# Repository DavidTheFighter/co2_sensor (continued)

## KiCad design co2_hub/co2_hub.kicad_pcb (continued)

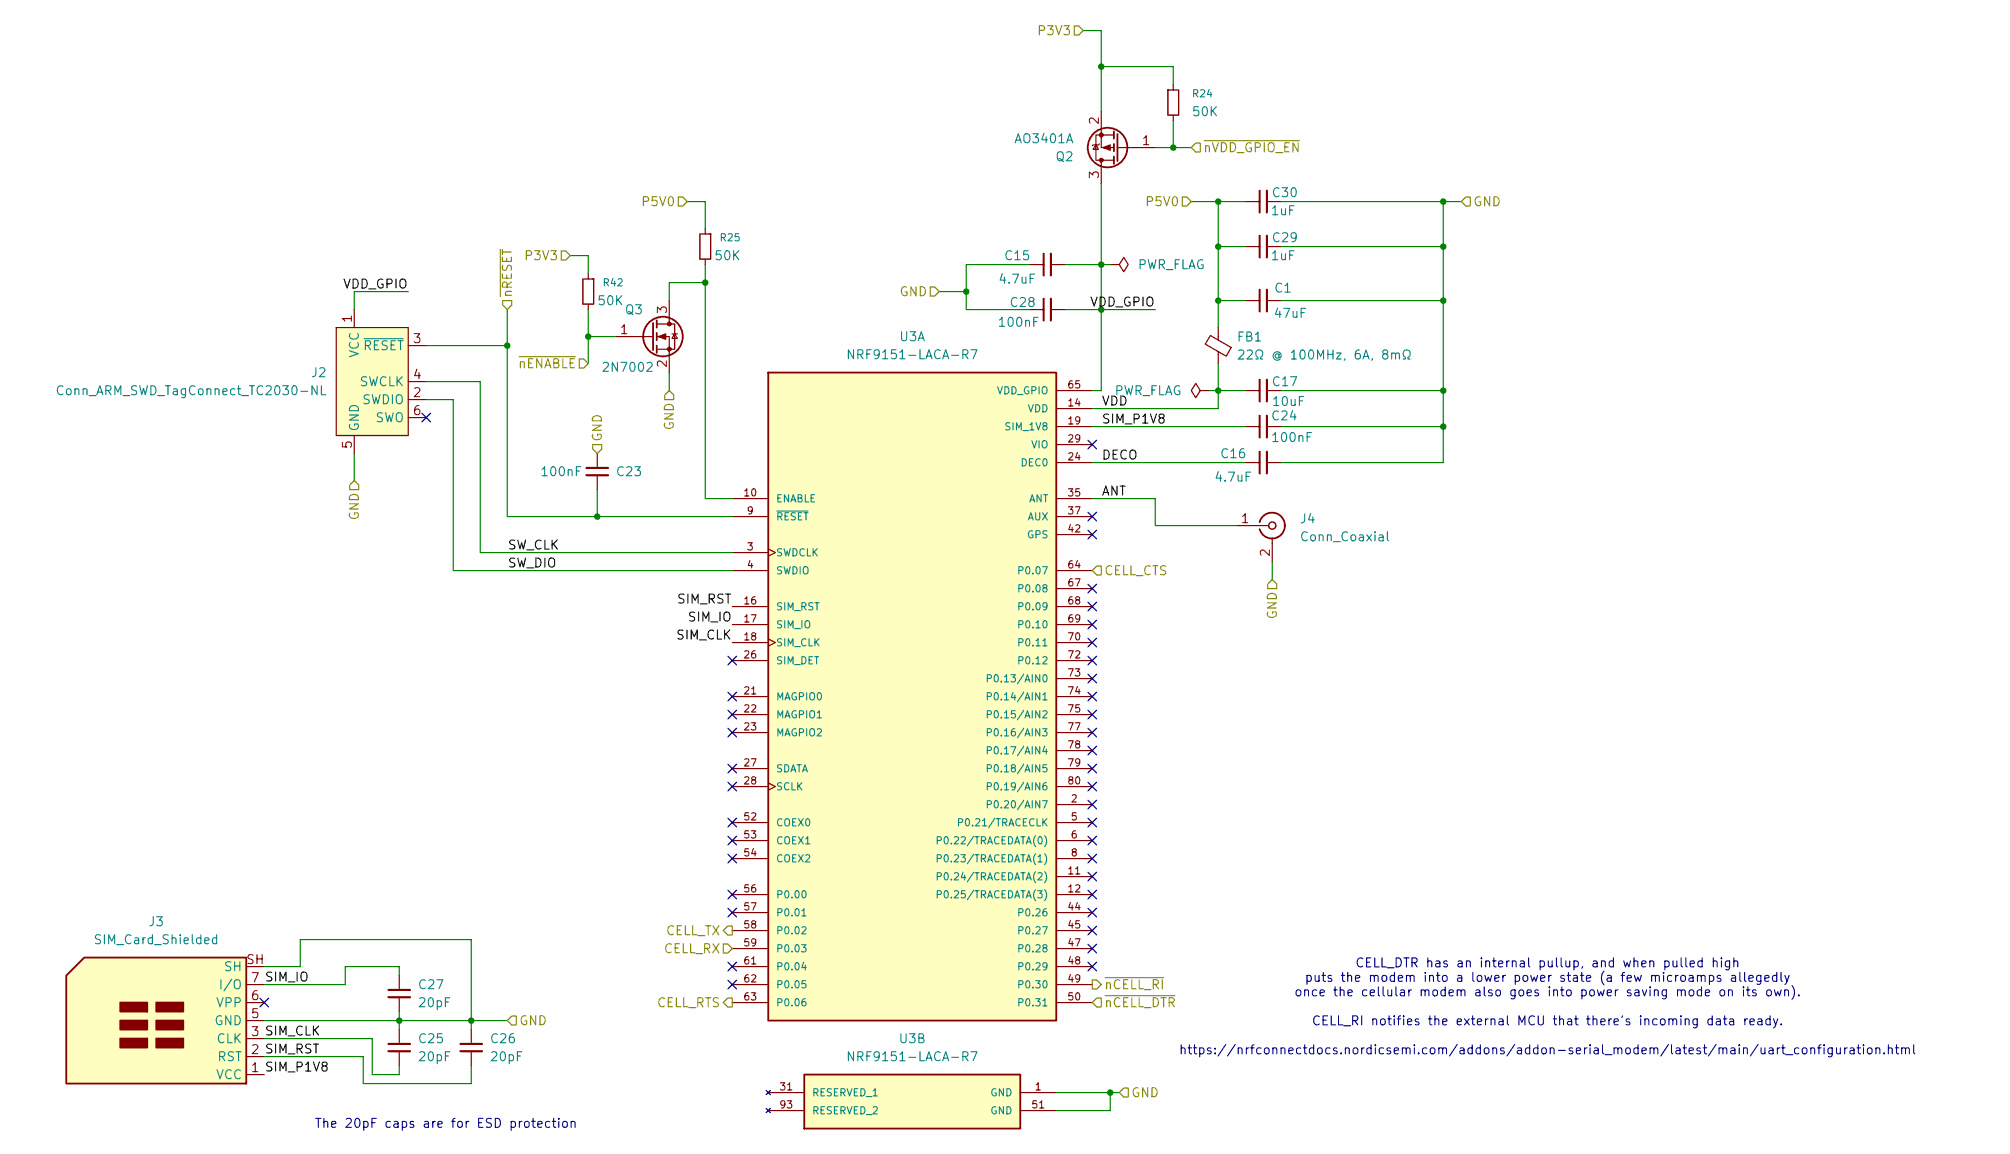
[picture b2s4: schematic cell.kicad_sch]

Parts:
C1: 47uF; C_1206_3216Metric; LCSC C96123
C15, C16: 4.7uF; C_0603_1608Metric; LCSC C19666
C17: 10uF; C_0805_2012Metric; LCSC C15850
C23, C24, C28: 100nF; C_0402_1005Metric; LCSC C1525
C25, C26, C27: 20pF; C_0402_1005Metric; LCSC C1554
C29, C30: 1uF; C_0603_1608Metric; LCSC C15849
FB1: 22Ω @ 100MHz, 6A, 8mΩ; L_0805_2012Metric; LCSC C361652
J2: Conn_ARM_SWD_TagConnect_TC2030-NL; Tag-Connect_TC2030-IDC-NL_2x03_P1.27mm_Vertical
J3: SIM_Card_Shielded; XUNPU Nano-SIM Push-Push With Card Detect; LCSC C7529384
J4: Conn_Coaxial; SMA_Samtec_SMA-J-P-H-ST-EM1_EdgeMount
Q2: AO3401A; SOT-23; LCSC C15127
Q3: 2N7002; SOT-23; LCSC C8545
R24, R25, R42: 50K; R_0402_1005Metric; LCSC C25794
U3: NRF9151-LACA-R7; Nordic_nRF9151-LAxx_LGA-80-33EP_12.1x11.1mm_P0.5mm; PARTREV 2025-10-21

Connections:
/MCU/LPUART1_CTS: U3.63 (P0.06); also elsewhere on the board
/MCU/LPUART1_RTS: U3.64 (P0.07); also elsewhere on the board
/MCU/LPUART1_RX: U3.58 (P0.02); also elsewhere on the board
/MCU/LPUART1_TX: U3.59 (P0.03); also elsewhere on the board
/MCU/~nCELL_DTR: U3.50 (P0.31); also elsewhere on the board
/MCU/~nCELL_ENABLE: Q3.1 (G), R42.2; also elsewhere on the board
/MCU/~nCELL_RI: U3.49 (P0.30); also elsewhere on the board
/MCU/~nCELL_VDD_GPIO_ENABLE: Q2.1 (G), R24.2; also elsewhere on the board
/P3V3: Q2.2 (S), R24.1, R42.1; also elsewhere on the board
/P5V0: C1.1, C29.1, C30.1, FB1.2, R25.1; also elsewhere on the board
/cell/ANT: J4.1 (In), U3.35 (ANT)
/cell/DECO: C16.1, U3.24 (DEC0)
/cell/SIM_CLK: C25.2, J3.3 (CLK), U3.18 (SIM_CLK)
/cell/SIM_IO: C27.1, J3.7 (I/O), U3.17 (SIM_IO)
/cell/SIM_P1V8: C24.2, J3.1 (VCC), U3.19 (SIM_1V8)
/cell/SIM_RST: C26.2, J3.2 (RST), U3.16 (SIM_RST)
/cell/SW_CLK: J2.4 (SWCLK), U3.3 (SWDCLK)
/cell/SW_DIO: J2.2 (SWDIO), U3.4 (SWDIO)
/cell/VDD: C17.1, FB1.1, U3.14 (VDD)
/cell/VDD_GPIO: C15.2, C28.2, J2.1 (VCC), Q2.3 (D), U3.65 (VDD_GPIO)
/cell/~nRESET: C23.2, J2.3 (~RESET), U3.9 (~RESET); also elsewhere on the board
GND: C1.2, C15.1, C16.2, C17.2, C23.1, C24.1, C25.1, C26.1, C27.2, C28.1, C29.2, C30.2, J2.5 (GND), J3.5 (GND), J3.SH, J4.2 (Ext), Q3.2 (S), U3.1 (GND), U3.7 (GND), U3.13 (GND), U3.15 (GND), U3.20 (GND), U3.25 (GND), U3.30 (GND), U3.34 (GND), U3.36 (GND), U3.38 (GND), U3.39 (GND), U3.40 (GND), U3.41 (GND), U3.43 (GND), U3.46 (GND), U3.51 (GND), U3.55 (GND), U3.60 (GND), U3.66 (GND), U3.71 (GND), U3.76 (GND), U3.105 (GND), U3.106 (GND), U3.107 (GND), U3.108 (GND), U3.109 (GND), U3.110 (GND), U3.111 (GND), U3.112 (GND), U3.113 (GND); also elsewhere on the board
unnamed: Q3.3 (D), R25.2, U3.10 (ENABLE)

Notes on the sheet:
CELL_DTR has an internal pullup, and when pulled high puts the modem into a lower power state (a few microamps allegedly once the cellular modem also goes into power saving mode on its own). CELL_RI notifies the external MCU that there's incoming data ready. https://nrfconnectdocs.nordicsemi.com/ad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
The 20pF caps are for ESD protection

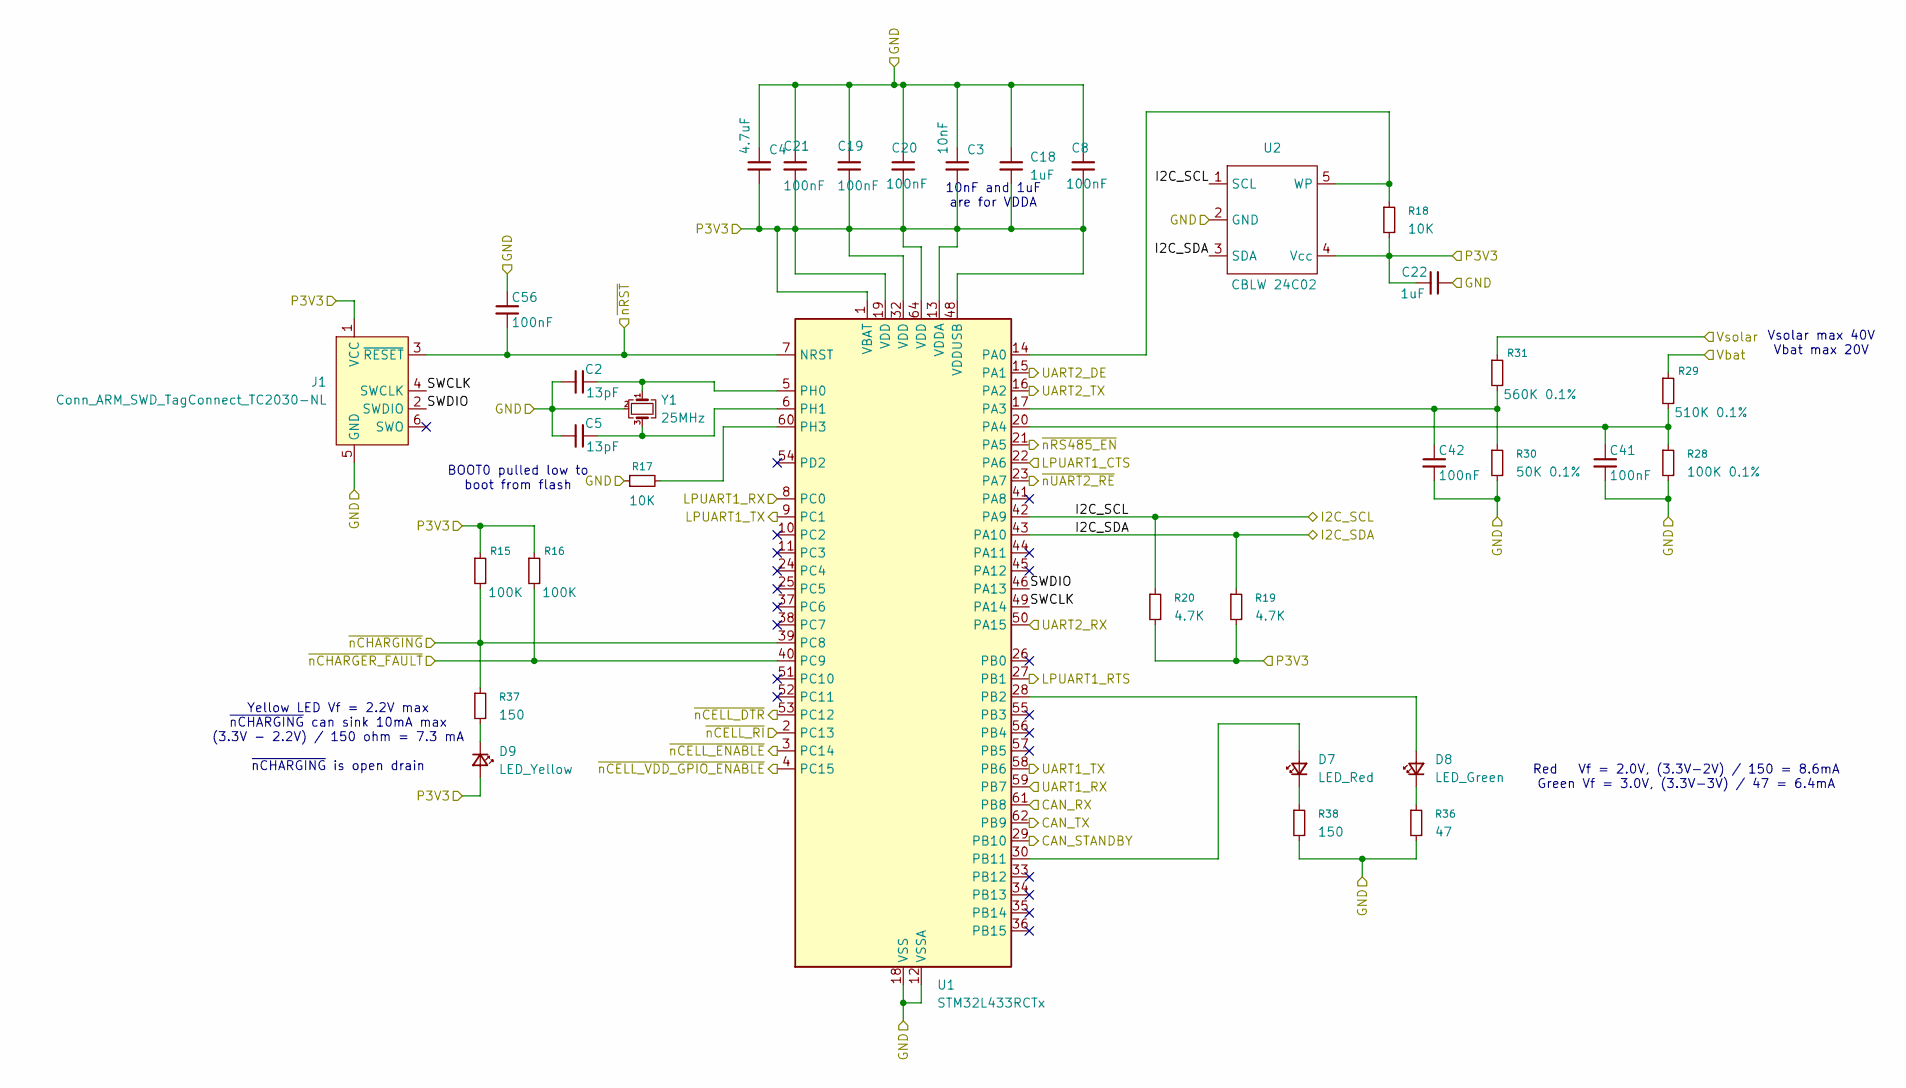
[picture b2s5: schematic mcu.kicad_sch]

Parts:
C2, C5: 13pF; C_0402_1005Metric; LCSC C1547
C3: 10nF; C_0402_1005Metric; LCSC C15195
C4: 4.7uF; C_0603_1608Metric; LCSC C19666
C8, C19, C20, C21, C41, C42, C56: 100nF; C_0402_1005Metric; LCSC C1525
C18, C22: 1uF; C_0603_1608Metric; LCSC C15849
D7: LED_Red; LED_0805_2012Metric; LCSC C84256
D8: LED_Green; LED_0805_2012Metric; LCSC C2297
D9: LED_Yellow; LED_0805_2012Metric; LCSC C2296
J1: Conn_ARM_SWD_TagConnect_TC2030-NL; Tag-Connect_TC2030-IDC-NL_2x03_P1.27mm_Vertical
R15, R16: 100K; R_0603_1608Metric; LCSC C25803
R17, R18: 10K; R_0402_1005Metric; LCSC C25744
R19, R20: 4.7K; R_0402_1005Metric; LCSC C25900
R28: 100K 0.1%; R_0603_1608Metric; LCSC C122538
R29: 510K 0.1%; R_0603_1608Metric; LCSC C861452
R30: 50K 0.1%; R_0603_1608Metric; LCSC C861451
R31: 560K 0.1%; R_0603_1608Metric; LCSC C719312
R36: 47; R_0603_1608Metric; LCSC C23182
R37, R38: 150; R_0603_1608Metric; LCSC C22808
U1: STM32L433RCTx; LQFP-64_10x10mm_P0.5mm; LCSC C160656
U2: CBLW 24C02; SOT-23-5; LCSC C18723540
Y1: 25MHz; Crystal_SMD_3225-4Pin_3.2x2.5mm; LCSC C251614

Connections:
/CAN/RX: U1.61 (PB8); also elsewhere on the board
/CAN/STANDBY: U1.29 (PB10); also elsewhere on the board
/CAN/TX: U1.62 (PB9); also elsewhere on the board
/DBG_UART_RX: U1.59 (PB7); also elsewhere on the board
/DBG_UART_TX: U1.58 (PB6); also elsewhere on the board
/I2C_SCL: R20.1, U1.42 (PA9), U2.1 (SCL); also elsewhere on the board
/I2C_SDA: R19.1, U1.43 (PA10), U2.3 (SDA); also elsewhere on the board
/MCU/LPUART1_CTS: U1.22 (PA6); also elsewhere on the board
/MCU/LPUART1_RTS: U1.27 (PB1); also elsewhere on the board
/MCU/LPUART1_RX: U1.8 (PC0); also elsewhere on the board
/MCU/LPUART1_TX: U1.9 (PC1); also elsewhere on the board
/MCU/SWCLK: J1.4 (SWCLK), U1.49 (PA14)
/MCU/SWDIO: J1.2 (SWDIO), U1.46 (PA13)
/MCU/UART2_DE: U1.15 (PA1); also elsewhere on the board
/MCU/UART2_RX: U1.50 (PA15); also elsewhere on the board
/MCU/UART2_TX: U1.16 (PA2); also elsewhere on the board
/MCU/~nCELL_DTR: U1.53 (PC12); also elsewhere on the board
/MCU/~nCELL_ENABLE: U1.3 (PC14); also elsewhere on the board
/MCU/~nCELL_RI: U1.2 (PC13); also elsewhere on the board
/MCU/~nCELL_VDD_GPIO_ENABLE: U1.4 (PC15); also elsewhere on the board
/MCU/~nCHARGER_FAULT: R16.2, U1.40 (PC9); also elsewhere on the board
/MCU/~nCHARGING: R15.2, R37.1, U1.39 (PC8); also elsewhere on the board
/MCU/~nRS485_EN: U1.21 (PA5); also elsewhere on the board
/MCU/~nRST: C56.2, J1.3 (~RESET), U1.7 (NRST); also elsewhere on the board
/MCU/~nUART2_RE: U1.23 (PA7); also elsewhere on the board
/P3V3: C3.2, C4.2, C8.2, C18.2, C19.2, C20.2, C21.2, C22.1, D9.2 (A), J1.1 (VCC), R15.1, R16.1, R18.2, R19.2, R20.2, U1.1 (VBAT), U1.13 (VDDA), U1.19 (VDD), U1.32 (VDD), U1.48 (VDDUSB), U1.64 (VDD), U2.4 (Vcc); also elsewhere on the board
/Vbus: R29.1; also elsewhere on the board
/Vsolar: R31.1; also elsewhere on the board
GND: C2.1, C3.1, C4.1, C5.1, C8.1, C18.1, C19.1, C20.1, C21.1, C22.2, C41.2, C42.2, C56.1, J1.5 (GND), R17.1, R28.2, R30.2, R36.2, R38.2, U1.12 (VSSA), U1.18 (VSS), U1.31 (VSS), U1.47 (VSS), U1.63 (VSS), U2.2 (GND), Y1.2 (G), Y1.4 (G); also elsewhere on the board
unnamed: D7.2 (A), U1.30 (PB11)
unnamed: D7.1 (K), R38.1
unnamed: D8.2 (A), U1.28 (PB2)
unnamed: D8.1 (K), R36.1
unnamed: D9.1 (K), R37.2
unnamed: R18.1, U1.14 (PA0), U2.5 (WP)
unnamed: C42.1, R30.1, R31.2, U1.17 (PA3)
unnamed: C41.1, R28.1, R29.2, U1.20 (PA4)
unnamed: C2.2, U1.5 (PH0), Y1.1
unnamed: C5.2, U1.6 (PH1), Y1.3
unnamed: R17.2, U1.60 (PH3)

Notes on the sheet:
Red Vf = 2.0V, (3.3V-2V) / 150 = 8.6mA Green Vf = 3.0V, (3.3V-3V) / 47 = 6.4mA
Yellow LED Vf = 2.2V max ~{nCHARGING} can sink 10mA max (3.3V - 2.2V) / 150 ohm = 7.3 mA ~{nCHARGING} is open drain
10nF and 1uF are for VDDA
BOOT0 pulled low to boot from flash
Vsolar max 40V Vbat max 20V

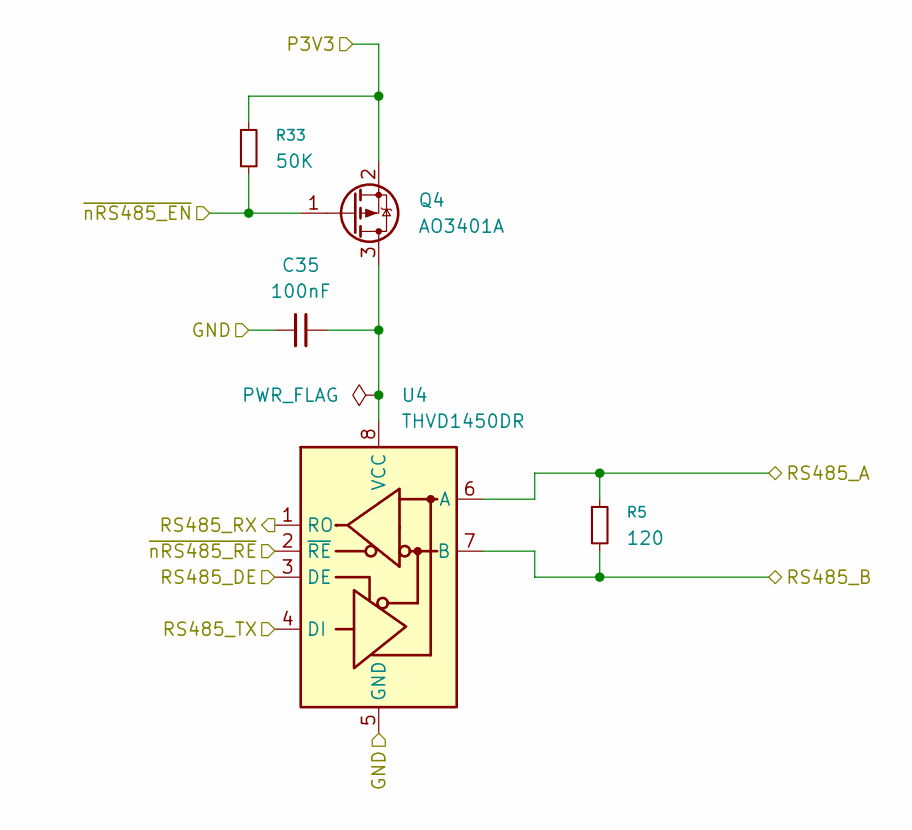
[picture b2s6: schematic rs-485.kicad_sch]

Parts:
C35: 100nF; C_0402_1005Metric; LCSC C1525
Q4: AO3401A; SOT-23; LCSC C15127
R5: 120; R_0603_1608Metric; LCSC C22787
R33: 50K; R_0402_1005Metric; LCSC C25794
U4: THVD1450DR; VSON-8-1EP_3x3mm_P0.65mm_EP1.6x2.4mm

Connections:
/MCU/UART2_DE: U4.3 (DE); also elsewhere on the board
/MCU/UART2_RX: U4.1 (RO); also elsewhere on the board
/MCU/UART2_TX: U4.4 (DI); also elsewhere on the board
/MCU/~nRS485_EN: Q4.1 (G), R33.2; also elsewhere on the board
/MCU/~nUART2_RE: U4.2 (~RE); also elsewhere on the board
/P3V3: Q4.2 (S), R33.1; also elsewhere on the board
/RS485_A: R5.1, U4.6 (A); also elsewhere on the board
/RS485_B: R5.2, U4.7 (B); also elsewhere on the board
GND: C35.1, U4.5 (GND); also elsewhere on the board
unnamed: C35.2, Q4.3 (D), U4.8 (VCC)

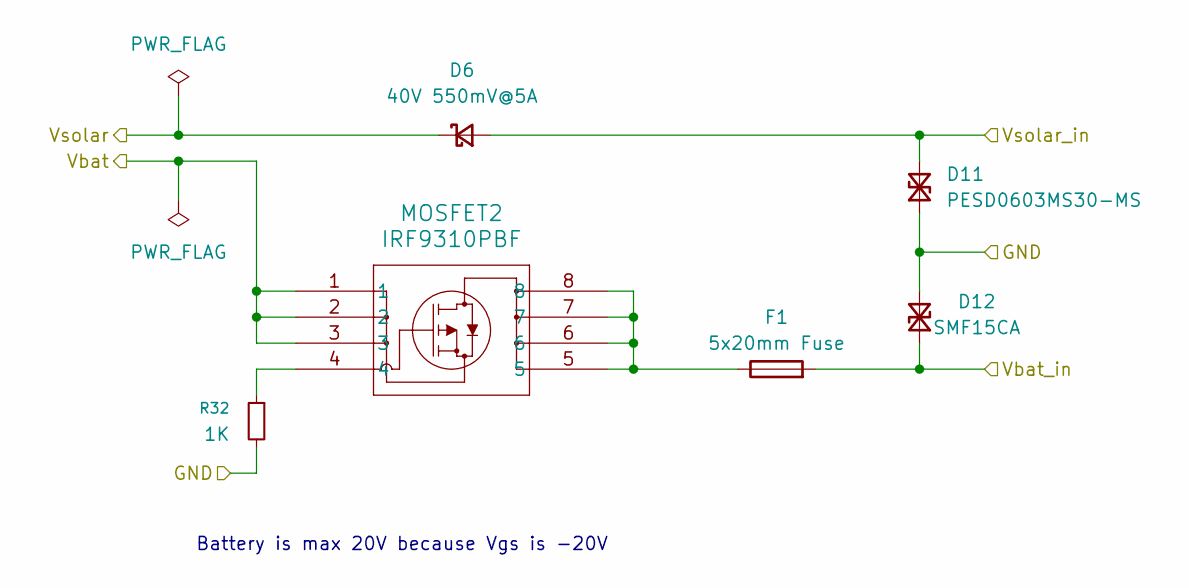
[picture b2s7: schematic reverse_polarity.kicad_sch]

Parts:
D6: 40V 550mV@5A; D_SMA; LCSC C22452
D11: PESD0603MS30-MS; D_0603_1608Metric; LCSC C7473181
D12: SMF15CA; D_SOD-123F; LCSC C19077510
F1: 5x20mm Fuse; Fuseholder_Clip-5x20mm_Bel_FC-203-22_Lateral_P17.80x5.00mm_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
MOSFET2: IRF9310PBF; SO-8_3.9x4.9mm_P1.27mm; LCSC C5236693
R32: 1K; R_0603_1608Metric; LCSC C21190

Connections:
/Vbat: MOSFET2.1, MOSFET2.2, MOSFET2.3; also elsewhere on the board
/Vbat_in: D12.1 (A1), F1.2; also elsewhere on the board
/Vsolar: D6.1 (K); also elsewhere on the board
/Vsolar_in: D6.2 (A), D11.2 (A2); also elsewhere on the board
GND: D11.1 (A1), D12.2 (A2), R32.2; also elsewhere on the board
unnamed: F1.1, MOSFET2.5, MOSFET2.6, MOSFET2.7, MOSFET2.8
unnamed: MOSFET2.4, R32.1

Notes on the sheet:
Battery is max 20V because Vgs is -20V

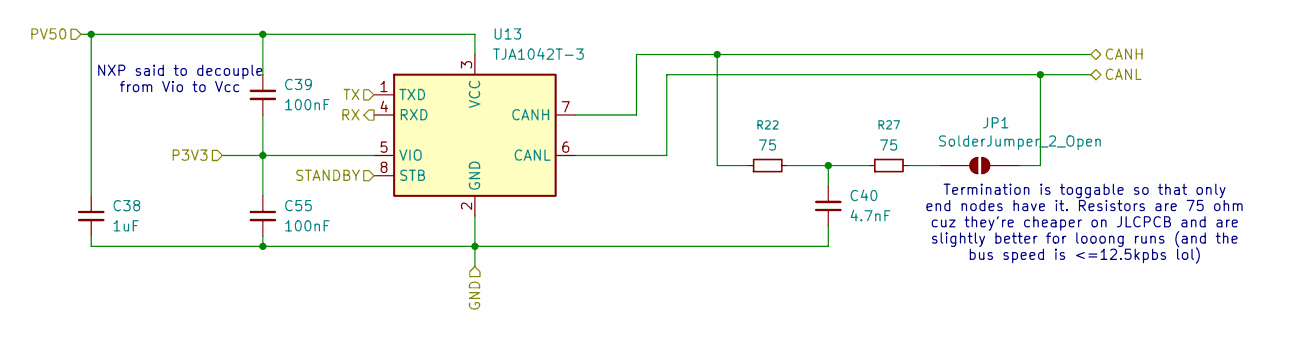
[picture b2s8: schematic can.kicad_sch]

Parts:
C38: 1uF; C_0603_1608Metric; LCSC C15849
C39, C55: 100nF; C_0402_1005Metric; LCSC C1525
C40: 4.7nF; C_0805_2012Metric; LCSC C1744
JP1: SolderJumper_2_Open; SolderJumper-2_P1.3mm_Open_TrianglePad1.0x1.5mm
R22, R27: 75; R_0603_1608Metric; LCSC C4275
U13: TJA1042T-3; SOIC-8_3.9x4.9mm_P1.27mm; LCSC C132227

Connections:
/CAN/RX: U13.4 (RXD); also elsewhere on the board
/CAN/STANDBY: U13.8 (STB); also elsewhere on the board
/CAN/TX: U13.1 (TXD); also elsewhere on the board
/CANH: R22.1, U13.7 (CANH); also elsewhere on the board
/CANL: JP1.2 (B), U13.6 (CANL); also elsewhere on the board
/P3V3: C39.2, C55.1, U13.5 (VIO); also elsewhere on the board
/P5V0: C38.1, C39.1, U13.3 (VCC); also elsewhere on the board
GND: C38.2, C40.2, C55.2, U13.2 (GND); also elsewhere on the board
unnamed: C40.1, R22.2, R27.1
unnamed: JP1.1 (A), R27.2

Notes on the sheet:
Termination is toggable so that only end nodes have it. Resistors are 75 ohm cuz they're cheaper on JLCPCB and are slightly better for looong runs (and the bus speed is <=12.5kpbs lol)
NXP said to decouple from Vio to Vcc

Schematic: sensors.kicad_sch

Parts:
C12, C13: 100nF; C_0402_1005Metric; LCSC C1525
U5: MS5611-01BA; LGA-8_3x5mm_P1.25mm; LCSC C15639
U6: SHT4x; Sensirion_DFN-4_1.5x1.5mm_P0.8mm_SHT4x_NoCentralPad; LCSC C2909890

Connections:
/I2C_SCL: U5.8 (SCLK), U6.2 (SCL); also elsewhere on the board
/I2C_SDA: U5.7 (SDI/SDA), U6.1 (SDA); also elsewhere on the board
/P3V3: C12.1, C13.1, U5.1 (VDD), U5.2 (PS), U6.3 (VDD); also elsewhere on the board
GND: C12.2, C13.2, U5.3 (GND), U5.4 (CSB), U5.5 (CSB), U6.4 (VSS); also elsewhere on the board

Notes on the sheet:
I2C = 1000100
CSB in I2C defines the I2C address LOW = 1110111
PS tied high for I2C mode

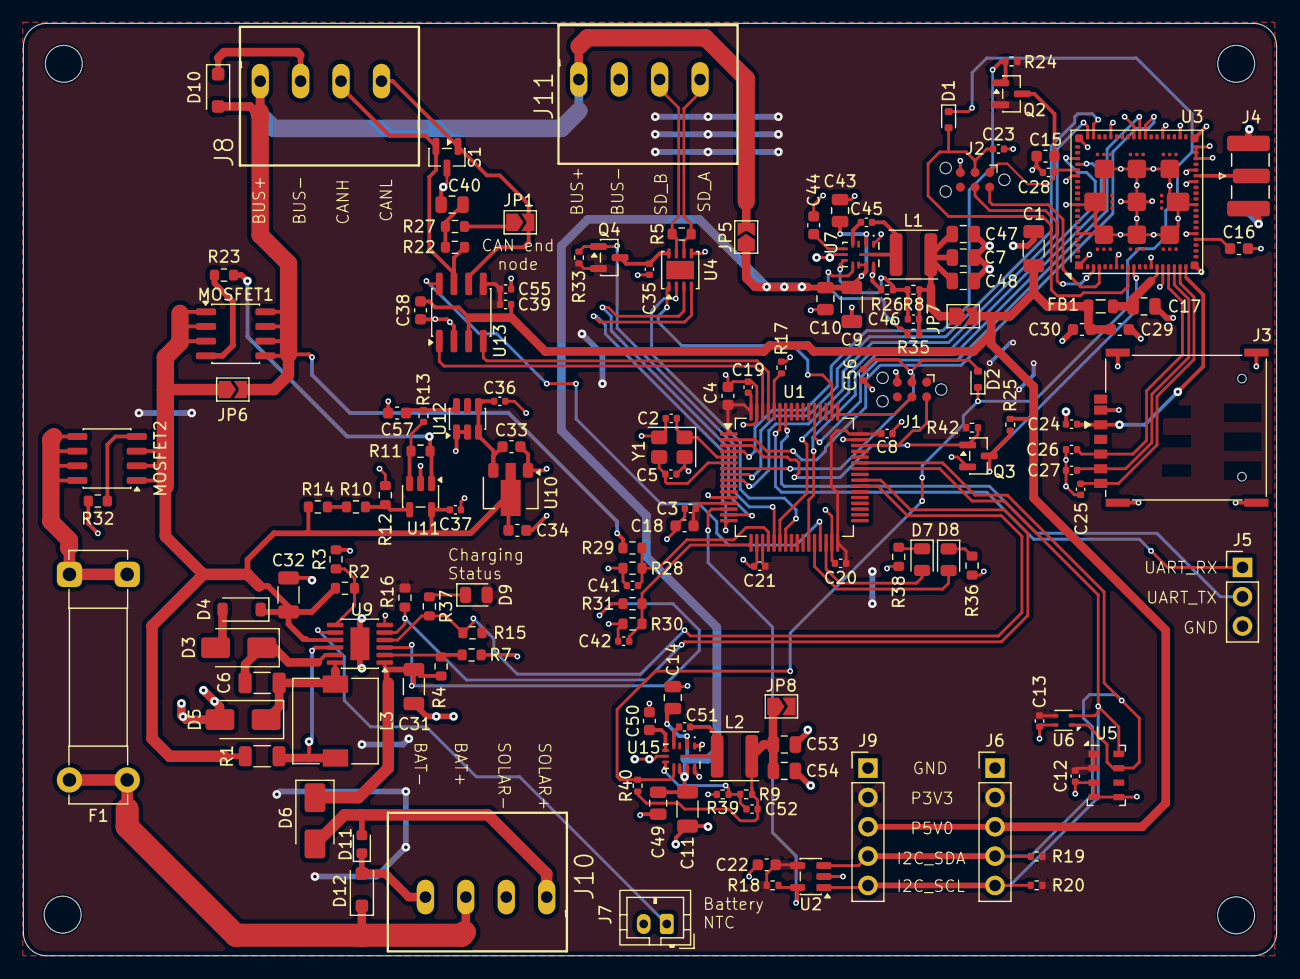
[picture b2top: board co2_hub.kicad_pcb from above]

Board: 4 copper layers, 108.5 x 80.7 mm, 152 parts (0 on the bottom side), 92 nets.

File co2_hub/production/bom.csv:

Designator,Footprint,Quantity,Value,LCSC Part #
C1,1206,1,47uF,C96123
"C10, C14, C43, C49",0805,4,220nF,C5378
"C11, C9",1206,2,4.7uF,C29823
"C12, C13, C19, C20, C21, C23, C24, C28, C35, C36, C37, C39, C41, C42, C45, C51, C55, C56, C8",0402,19,100nF,C1525
"C15, C16, C4",0603,3,4.7uF,C19666
"C17, C47, C48, C53, C54",0805,5,10uF,C15850
"C18, C22, C29, C30, C33, C34, C38, C44, C50, C57",0603,10,1uF,C15849
"C2, C5",0402,2,13pF,C1547
"C25, C26, C27, C46, C52",0402,5,20pF,C1554
C3,0402,1,10nF,C15195
"C31, C32",1206,2,10uF,C13585
C40,0805,1,4.7nF,C1744
C6,1206,1,1uF,C1848
C7,0805,1,22uF,C45783
"D1, D2",D_SOD-523,2,40V 0.3V@0.2A,C135802
"D10, D12",D_SOD-123F,2,SMF15CA,C19077510
D11,0603,1,PESD0603MS30-MS,C7473181
D3,D_SMA,1,40V 550mV@3A,C8678
D4,D_SOD-123,1,Zener 6.2V,C22435091
"D5, D6",D_SMA,2,40V 550mV@5A,C22452
D7,0805,1,LED_Red,C84256
D8,0805,1,LED_Green,C2297
D9,0805,1,LED_Yellow,C2296
F1,Fuseholder_Clip-5x20mm_Bel_FC-203-22_Lateral_P17.80x5.00mm_D1.17mm_Horizontal,1,5x20mm Fuse,
FB1,0805,1,"22Ω @ 100MHz, 6A, 8mΩ",C361652
"J10, J11, J8",WAGO-250-104,3,Conn_01x04,
J3,XUNPU Nano-SIM Push-Push With Card Detect,1,SIM_Card_Shielded,C7529384
J4,SMA_Samtec_SMA-J-P-H-ST-EM1_EdgeMount,1,Conn_Coaxial,
J5,PinHeader_1x03_P2.54mm_Vertical,1,Conn_01x03,
"J6, J9",PinHeader_1x05_P2.54mm_Vertical,2,Conn_01x05,
J7,JST_PH_B2B-PH-K_1x02_P2.00mm_Vertical,1,Conn_01x02,
"L1, L2",L_Changjiang_FNR4030S,2,10uH,C167879
L3,L_7.3x7.3_H4.5,1,10uH,C19268627
"MOSFET1, MOSFET2",SO-8_3.9x4.9mm_P1.27mm,2,IRF9310PBF,C5236693
"Q2, Q4",SOT-23,2,AO3401A,C15127
Q3,SOT-23,1,2N7002,C8545
R1,1206,1,0.05,C7467249
R10,0603,1,887K 0.1%,C2984370
R11,0603,1,4.64M 1%,C482862
"R12, R28",0603,2,100K 0.1%,C122538
"R13, R17, R18",0402,3,10K,C25744
R14,0603,1,16.2K 0.1%,C728602
"R15, R16, R7",0603,3,100K,C25803
"R19, R20",0402,2,4.7K,C25900
R2,0603,1,1.05M,C5126052
"R22, R27",0603,2,75,C4275
R23,0603,1,2.7K,C13167
"R24, R25, R33, R42",0402,4,50K,C25794
R26,0402,1,24.9K,C138027
R29,0603,1,510K 0.1%,C861452
R3,0603,1,330K,C23137
R30,0603,1,50K 0.1%,C861451
R31,0603,1,560K 0.1%,C719312
R32,0603,1,1K,C21190
"R35, R40, R8, R9",0402,4,100K,C25741
R36,0603,1,47,C23182
"R37, R38",0603,2,150,C22808
R39,0402,1,43.2K,C2906870
R4,0603,1,510K,C23192
R5,0603,1,120,C22787
S1,SOT-23,1,PESD2CAN,C2687131
U1,LQFP-64_10x10mm_P0.5mm,1,STM32L433RCTx,C160656
U10,SOT-89-3,1,HT7533-1-SOT89,C14289
U11,SOT-23-5,1,TLV1831DBVR,C22427370
U12,SOT-23-6,1,REF35125QDBVR,C7043252
U13,SOIC-8_3.9x4.9mm_P1.27mm,1,TJA1042T-3,C132227
U15,LMR36006xxxxx,1,LMR36006xxxxx,C1850367
U2,SOT-23-5,1,CBLW 24C02,C18723540
U3,Nordic_nRF9151-LAxx_LGA-80-33EP_12.1x11.1mm_P0.5mm,1,NRF9151-LACA-R7,
U4,VSON-8-1EP_3x3mm_P0.65mm_EP1.6x2.4mm,1,THVD1450DR,
U5,LGA-8_3x5mm_P1.25mm,1,MS5611-01BA,C15639
U6,Sensirion_DFN-4_1.5x1.5mm_P0.8mm_SHT4x_NoCentralPad,1,SHT4x,C2909890
U7,LMR36006xxxxx,1,LMR36015,C2867810
U9,MSOP-12-1EP_3x4.039mm_P0.65mm_EP1.651x2.845mm,1,LT3652IMSE,C671115
Y1,Crystal_SMD_3225-4Pin_3.2x2.5mm,1,25MHz,C251614

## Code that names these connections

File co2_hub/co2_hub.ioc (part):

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Mcu.Name=STM32L433R(B-C)Tx
Mcu.Package=LQFP64
Mcu.UserName=STM32L433RCTx
PA10.Mode=I2C
PA10.Signal=I2C1_SDA
PA13\ (JTMS-SWDIO).Mode=Serial_Wire
PA13\ (JTMS-SWDIO).Signal=SYS_JTMS-SWDIO
PA14\ (JTCK-SWCLK).Mode=Serial_Wire
PA14\ (JTCK-SWCLK).Signal=SYS_JTCK-SWCLK
PA3.Signal=ADCx_IN8
PA4.Signal=ADCx_IN9
PA6.Mode=CTS_RTS
PA6.Signal=LPUART1_CTS
PA9.Mode=I2C
PA9.Signal=I2C1_SCL
PB1.Mode=CTS_RTS
PB1.Signal=LPUART1_RTS
PB6.Mode=Asynchronous
PB6.Signal=USART1_TX
PB7.Mode=Asynchronous
PB7.Signal=USART1_RX
PB8.Mode=CAN_Activate
PB8.Signal=CAN1_RX
PB9.Mode=CAN_Activate
PB9.Signal=CAN1_TX
PC0.Mode=Asynchronous
PC0.Signal=LPUART1_RX
PC1.Mode=Asynchronous
PC1.Signal=LPUART1_TX
PH0-OSC_IN\ (PH0).Mode=HSE-External-Oscillator
PH0-OSC_IN\ (PH0).Signal=RCC_OSC_IN
PH1-OSC_OUT\ (PH1).Mode=HSE-External-Oscillator
PH1-OSC_OUT\ (PH1).Signal=RCC_OSC_OUT
RCC.HSE_VALUE=25000000
RCC.SYSCLKFreq_VALUE=80000000
RCC.SYSCLKSource=RCC_SYSCLKSOURCE_PLLCLK
board=custom

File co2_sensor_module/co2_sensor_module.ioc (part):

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Mcu.Name=STM32L432K(B-C)Ux
Mcu.Package=UFQFPN32
Mcu.UserName=STM32L432KBUx
PA10.Mode=I2C
PA10.Signal=I2C1_SDA
PA11.Mode=CAN_Activate
PA11.Signal=CAN1_RX
PA12.Mode=CAN_Activate
PA12.Signal=CAN1_TX
PA13\ (JTMS-SWDIO).Mode=Serial_Wire
PA13\ (JTMS-SWDIO).Signal=SYS_JTMS-SWDIO
PA14\ (JTCK-SWCLK).Mode=Serial_Wire
PA14\ (JTCK-SWCLK).Signal=SYS_JTCK-SWCLK
PA2.Mode=Asynchronous
PA2.Signal=LPUART1_TX
PA3.Mode=Asynchronous
PA3.Signal=LPUART1_RX
PA9.Mode=I2C
PA9.Signal=I2C1_SCL
RCC.HSE_VALUE=8000000
board=custom
